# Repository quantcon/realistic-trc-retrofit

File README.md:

# Realistic CB Radio Retrofit Project
Assets for retrofitting a Realistic TRC-219 with Teensy 3.2

# Required tools:

* KiCad PCB
    * http://kicad.org/
* Arduino IDE
    * https://www.arduino.cc/en/Main/Software
* Teensy Microcontroller
    * https://www.pjrc.com/store/teensy32.html
* PCB Fabricator
    * https://oshpark.com/ (or similar!)

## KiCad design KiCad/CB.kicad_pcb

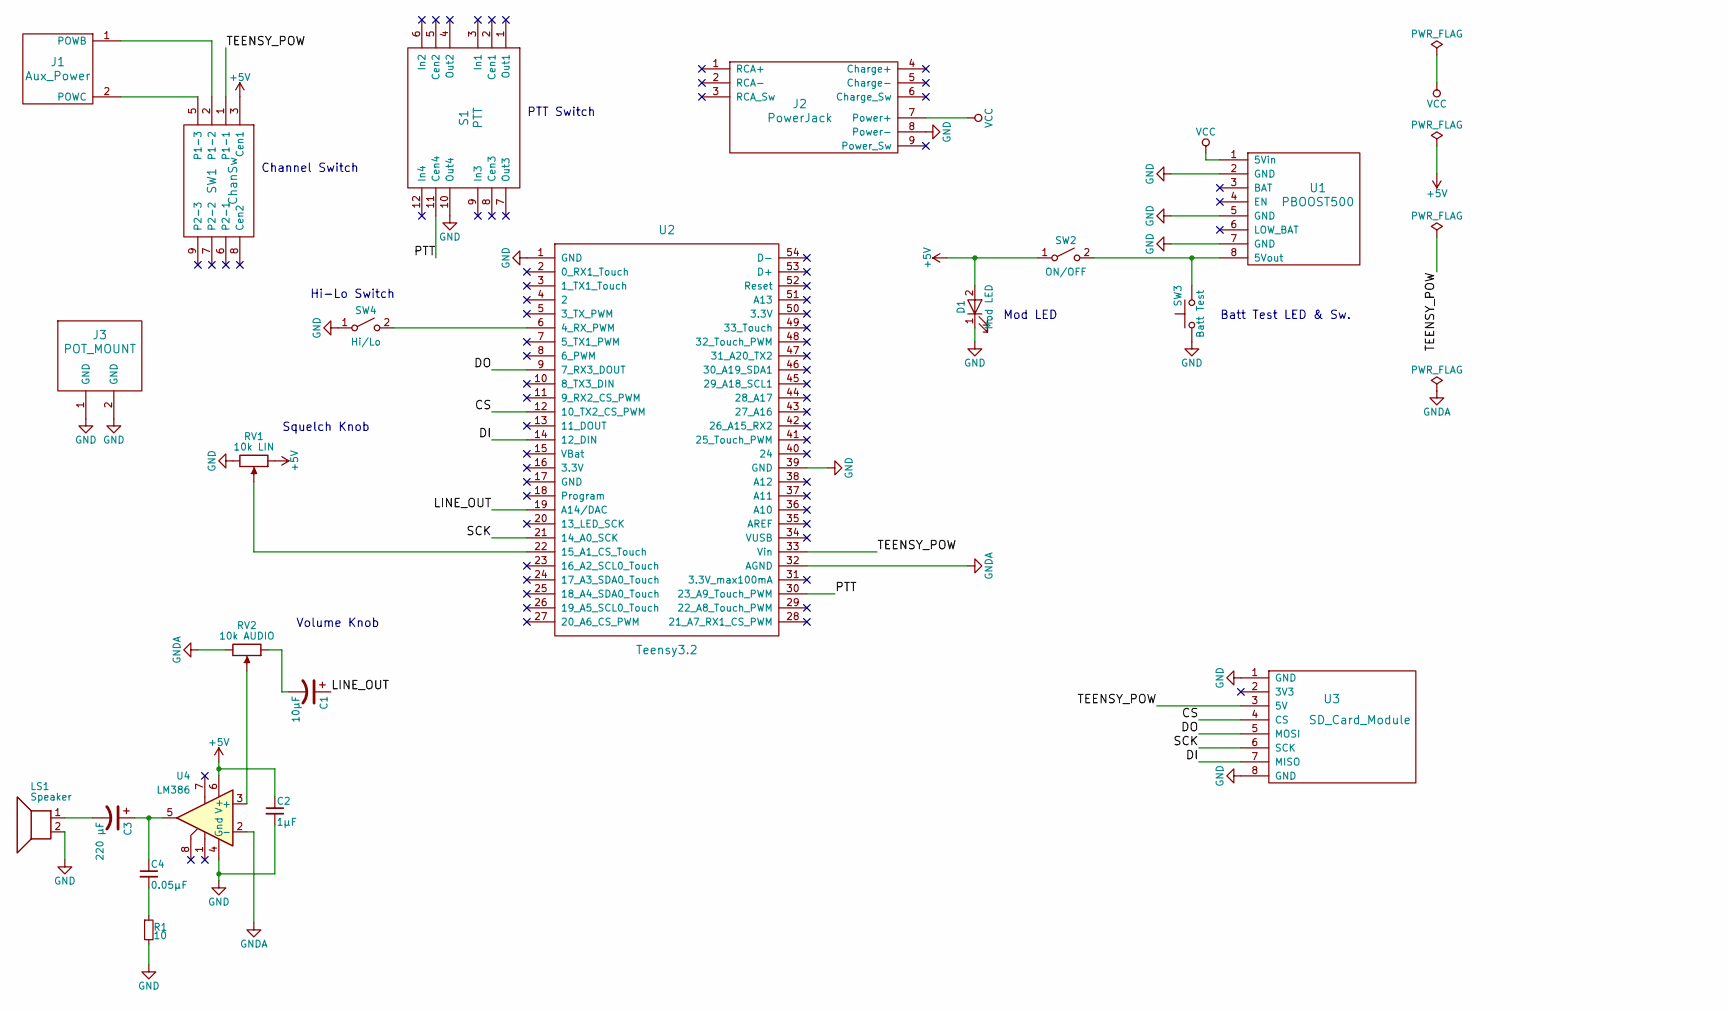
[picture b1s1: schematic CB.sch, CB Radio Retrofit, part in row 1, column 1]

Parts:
C1: 10µF; C_Disc_D6.0mm_W2.5mm_P5.00mm
C2: 1µF; C_Disc_D6.0mm_W2.5mm_P5.00mm
C3: 220 µF; C_Disc_D6.0mm_W2.5mm_P5.00mm
C4: 0.05µF; C_Disc_D6.0mm_W2.5mm_P5.00mm
D1: Mod LED; JST_EH_B02B-EH-A_02x2.50mm_Straight
J1: Aux_Power; Pin_Header_Straight_1x02
J2: PowerJack; Power_Jack
J3: POT_MOUNT
LS1: Speaker; JST_EH_B02B-EH-A_02x2.50mm_Straight
R1: 10; Resistor_Vertical_RM5mm
RV1: 10k LIN; JST_EH_B03B-EH-A_03x2.50mm_Straight
RV2: 10k AUDIO; JST_EH_B03B-EH-A_03x2.50mm_Straight
S1: PTT; 4pdt
SW1: ChanSw; 3pdt
SW2: ON/OFF; JST_EH_B02B-EH-A_02x2.50mm_Straight
SW3: Batt Test; JST_EH_B02B-EH-A_02x2.50mm_Straight
SW4: Hi/Lo; JST_EH_B02B-EH-A_02x2.50mm_Straight
U1: PBOOST500; Pin_Header_Straight_1x08
U2: Teensy3.2; Teensy30_31_32_LC
U3: SD_Card_Module; Pin_Header_Straight_1x08
U4: LM386; DIP-8_W7.62mm

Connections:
+5V: C2.1, D1.2 (A), RV1.1, SW1.3 (Cen1), SW2.1 (A), U4.6 (V+)
/CS: U2.12 (10_TX2_CS_PWM), U3.4 (CS)
/DI: U2.14 (12_DIN), U3.7 (MISO)
/DO: U2.9 (7_RX3_DOUT), U3.5 (MOSI)
/LINE_OUT: C1.1, U2.19 (A14/DAC)
/PTT: S1.11 (Cen4), U2.30 (23_A9_Touch_PWM)
/SCK: U2.21 (14_A0_SCK), U3.6 (SCK)
/TEENSY_POW: SW1.1 (P1-1), U2.33 (Vin), U3.3 (5V)
GND: C2.2, D1.1 (K), J2.8 (Power-), J3.1, J3.2, LS1.2, R1.2, RV1.3, S1.10 (Out4), SW3.1, SW4.1 (A), U1.2 (GND), U1.5 (GND), U1.7 (GND), U2.1 (GND), U2.39 (GND), U3.1 (GND), U3.8 (GND), U4.4 (Gnd)
GNDA: RV2.3, U2.32 (AGND), U4.2 (-)
unnamed: C1.2, RV2.1
unnamed: C3.1, C4.1, U4.5
unnamed: C3.2, LS1.1
unnamed: C4.2, R1.1
unnamed: J1.1 (POWB), SW1.2 (P1-2)
unnamed: J1.2 (POWC), SW1.5 (P1-3)
unnamed: RV1.2, U2.22 (15_A1_CS_Touch)
unnamed: RV2.2, U4.3 (+)
unnamed: SW2.2 (B), SW3.2, U1.8 (5Vout)
unnamed: SW4.2 (B), U2.6 (4_RX_PWM)
VCC: J2.7 (Power+), U1.1 (5Vin)

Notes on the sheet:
PTT Switch
Channel Switch
Volume Knob
Squelch Knob
Batt Test LED & Sw.
Mod LED
Hi-Lo Switch

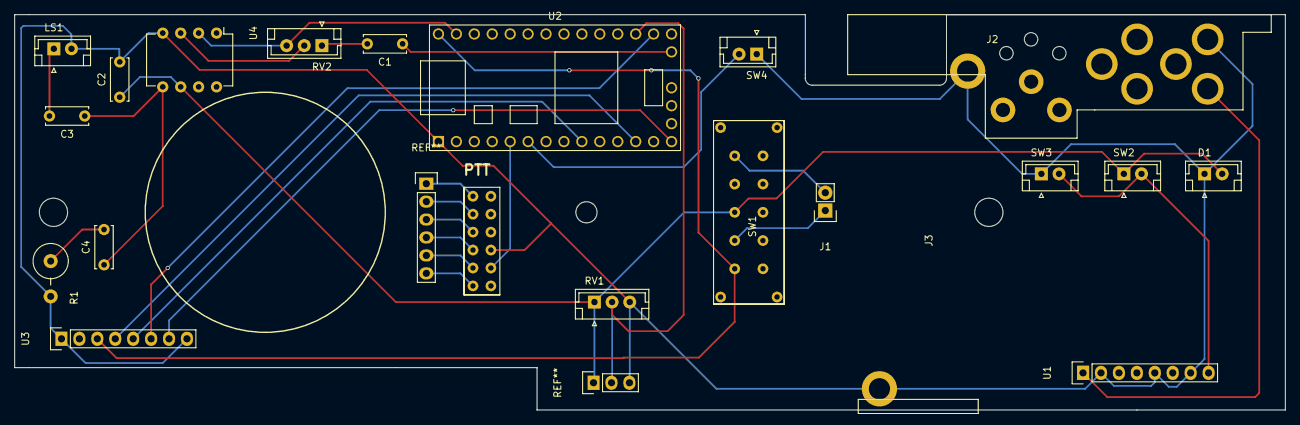
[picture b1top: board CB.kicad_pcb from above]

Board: 2 copper layers, 180.0 x 56.0 mm, 21 parts (0 on the bottom side), 21 nets.

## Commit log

2018-01-03 Added initial files
2021-11-10 Update README.md
    https://forum.kicad.info/t/warning-avoid-all-links-to-kicad-pcb-org-use-kicad-org/31521
